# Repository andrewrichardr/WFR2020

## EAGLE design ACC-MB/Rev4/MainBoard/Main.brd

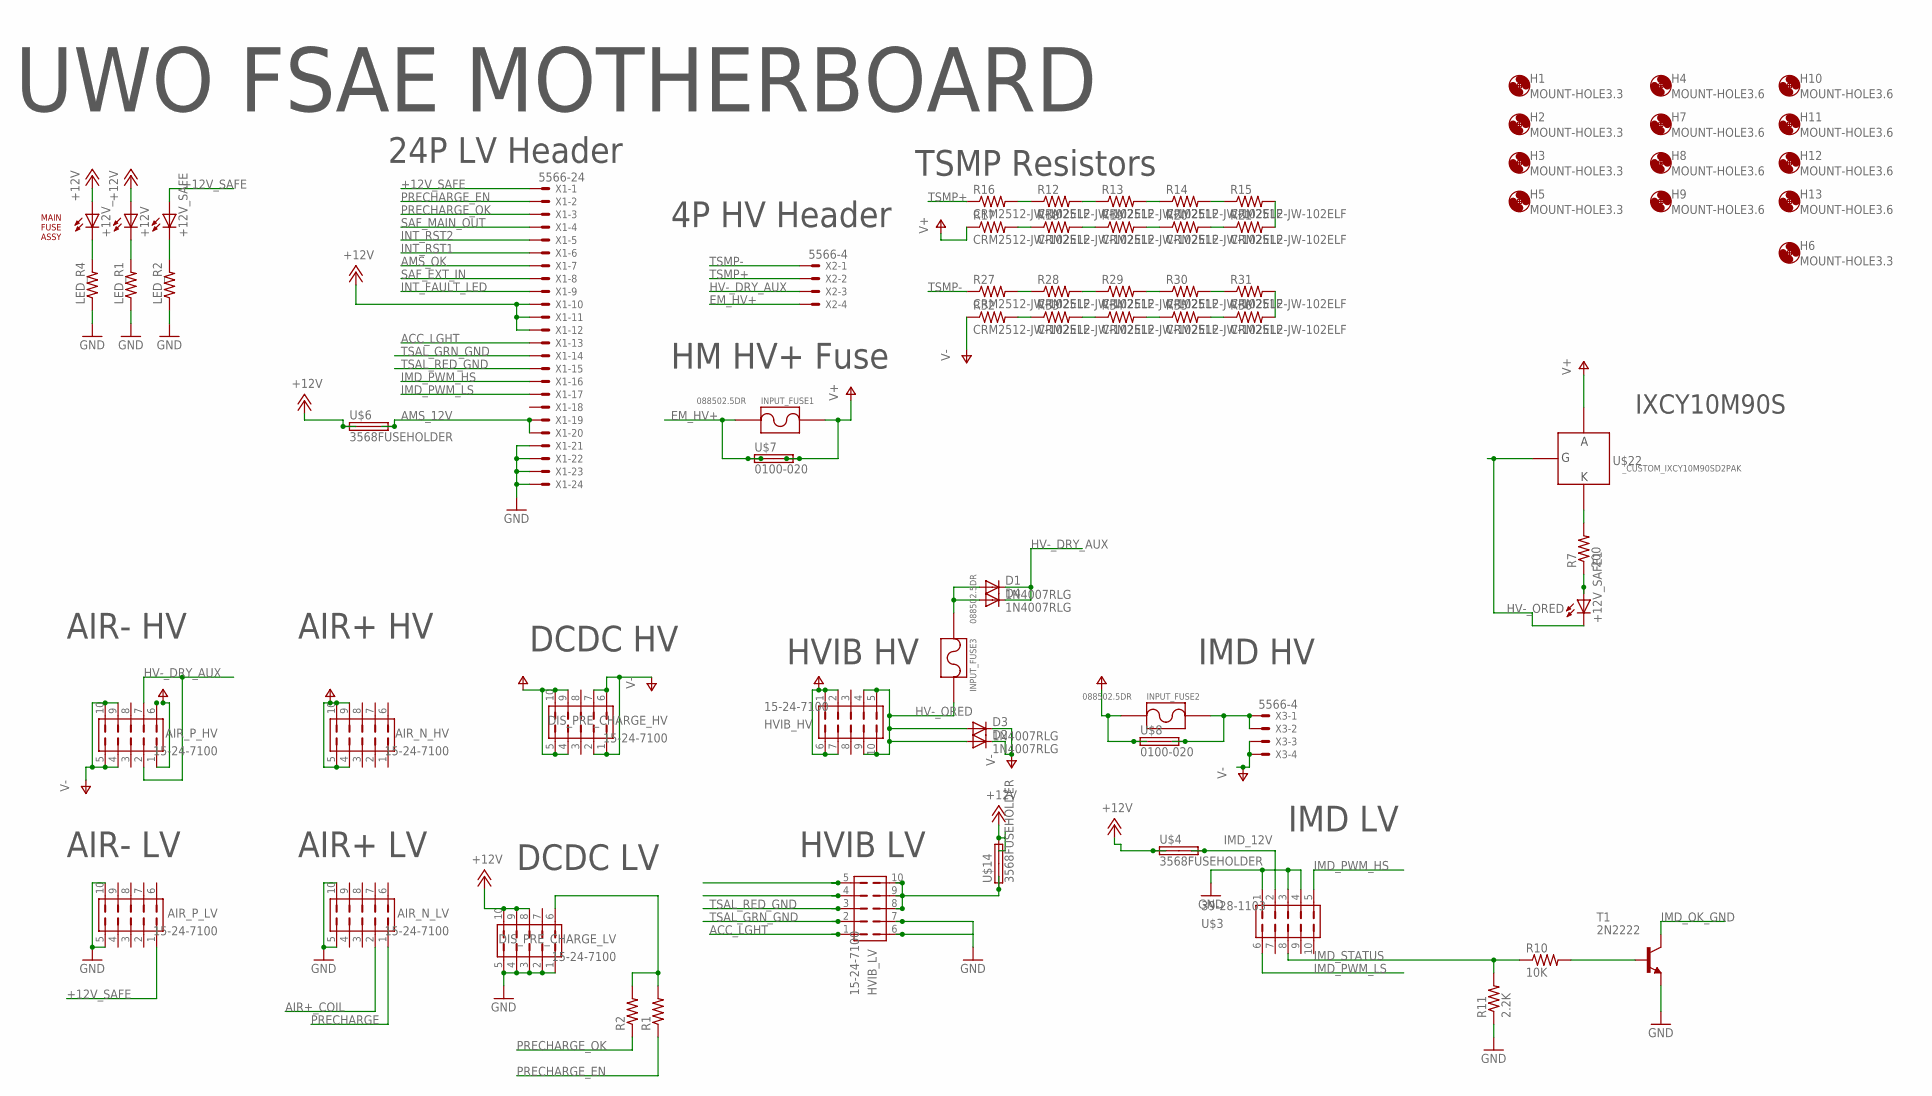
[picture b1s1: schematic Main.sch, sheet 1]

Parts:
+12V, +12V_, +12V_SAFE: LEDCHIP-LED0805; CHIP-LED0805
+12V_SAFE1: LED5MM
AIR_N_HV: 15-24-7100; 5566-10-BMI
AIR_N_LV: 15-24-7100; 5566-10-BMI
AIR_P_HV: 15-24-7100; 5566-10-BMI
AIR_P_LV: 15-24-7100; 5566-10-BMI
D1, D2, D3, D4: 1N4007RLG; DO41-10
DIS_PRE_CHARGE_HV: 15-24-7100; 5566-10-BMI
DIS_PRE_CHARGE_LV: 15-24-7100; 5566-10-BMI
H1, H2, H3, H5, H6: MOUNT-HOLE3.3; 3,3
H4, H7, H8, H9, H10, H11, H12, H13: MOUNT-HOLE3.6; 3,6
HVIB_HV: 15-24-7100; 5566-10-BMI
HVIB_LV: 15-24-7100; 5566-10-BMI
INPUT_FUSE1, INPUT_FUSE2, INPUT_FUSE3: 088502.5DR; _CUSTOM_PARTS_LF_885
LED_R1, LED_R2, LED_R4: R-US_R0805; R0805
R1, R2: R-US_R0805; R0805
R7: 200; R2010
R10: 10K; M0805
R11: 2.2K; M0805
R12, R13, R14, R15, R16, R17, R18, R19, R20, R21, R27, R28, R29, R30, R31, R32, R33, R34, R35, R36: CRM2512-JW-102ELF; R2512
T1: 2N2222; TO92-EBC-OVAL
U$1: MAINFUSEASSY
U$3: 39-28-1103
U$4, U$6, U$14: 3568FUSEHOLDER; 3568
U$7, U$8: 0100-020
U$22: _CUSTOM_IXCY10M90SD2PAK; TO228P991X238-3
X1: 5566-24
X2, X3: 5566-4

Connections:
+12V: +12V.A, +12V_.A, DIS_PRE_CHARGE_LV.8, DIS_PRE_CHARGE_LV.9, DIS_PRE_CHARGE_LV.10, U$4.L1 (1A), U$4.L2 (1B), U$6.L1 (1A), U$6.L2 (1B), U$14.R1 (2A), U$14.R2 (2B), X1.10, X1.11, X1.12; also elsewhere on the board
+12V_SAFE: +12V_SAFE.A, AIR_P_LV.1, X1.1; also elsewhere on the board
ACC_LGHT: HVIB_LV.1, X1.13
AIR+_COIL: AIR_N_LV.2; also elsewhere on the board
AMS_12V: U$6.R1 (2A), U$6.R2 (2B), X1.19, X1.20
AMS_OK: X1.7; also elsewhere on the board
EM_HV+: INPUT_FUSE1.P$1, U$7.P$1 (1A), U$7.P$3 (1B), X2.4
GND: AIR_N_LV.5, AIR_N_LV.10, AIR_P_LV.5, AIR_P_LV.10, DIS_PRE_CHARGE_LV.1, DIS_PRE_CHARGE_LV.2, DIS_PRE_CHARGE_LV.3, DIS_PRE_CHARGE_LV.4, DIS_PRE_CHARGE_LV.5, HVIB_LV.7, LED_R1.1, LED_R2.1, LED_R4.1, R11.1, T1.E, U$3.1, U$3.3, U$3.4, X1.21, X1.22, X1.23, X1.24; also elsewhere on the board
HV-_DRY_AUX: AIR_P_HV.2, AIR_P_HV.7, D1.C, D4.C, X2.3
HV-_ORED: +12V_SAFE1.K (C), D2.A, D3.A, HVIB_HV.4, HVIB_HV.5, HVIB_HV.9, HVIB_HV.10, INPUT_FUSE3.P$2, U$22.1 (G)
IMD_12V: U$3.2, U$4.R1 (2A), U$4.R2 (2B)
IMD_OK_GND: T1.C; also elsewhere on the board
IMD_PWM_HS: U$3.5, X1.16
IMD_PWM_LS: U$3.6, X1.17
IMD_STATUS: R10.1, R11.2, U$3.8
INT_FAULT_LED: X1.9; also elsewhere on the board
INT_RST1: X1.6; also elsewhere on the board
INT_RST2: X1.5; also elsewhere on the board
unnamed: +12V.C, LED_R1.2
unnamed: R10.2, T1.B
unnamed: +12V_.C, LED_R4.2
unnamed: +12V_SAFE.C, LED_R2.2
unnamed: R12.1, R16.2
unnamed: R12.2, R13.1
unnamed: R13.2, R14.1
unnamed: R14.2, R15.1
unnamed: R15.2, R21.2
unnamed: R20.2, R21.1
unnamed: R19.2, R20.1
unnamed: R18.2, R19.1
unnamed: R17.2, R18.1
unnamed: DIS_PRE_CHARGE_LV.6, R1.2, R2.2
unnamed: INPUT_FUSE2.P$2, U$8.P$2 (2A), U$8.P$4 (2B), X3.1, X3.2
unnamed: R7.2, U$22.2 (K)
unnamed: R27.2, R28.1
unnamed: R28.2, R29.1
unnamed: R29.2, R30.1
unnamed: R30.2, R31.1
unnamed: R31.2, R36.2
unnamed: R35.2, R36.1
unnamed: R34.2, R35.1
unnamed: R33.2, R34.1
unnamed: R32.2, R33.1
unnamed: +12V_SAFE1.A, R7.1
unnamed: HVIB_LV.8, HVIB_LV.9, HVIB_LV.10, U$14.L1 (1A), U$14.L2 (1B)
unnamed: D1.A, D4.A, INPUT_FUSE3.P$1
PRECHARGE: AIR_N_LV.1; also elsewhere on the board
PRECHARGE_EN: R1.1, X1.2; also elsewhere on the board
PRECHARGE_OK: R2.1, X1.3; also elsewhere on the board
SAF_EXT_IN: X1.8; also elsewhere on the board
SAF_MAIN_OUT: X1.4; also elsewhere on the board
TSAL_GRN_GND: HVIB_LV.2, X1.14
TSAL_RED_GND: HVIB_LV.3, X1.15
TSMP+: R16.1, X2.2
TSMP-: R27.1, X2.1
V+: AIR_N_HV.4, AIR_N_HV.5, AIR_N_HV.9, AIR_N_HV.10, AIR_P_HV.1, AIR_P_HV.6, DIS_PRE_CHARGE_HV.4, DIS_PRE_CHARGE_HV.5, DIS_PRE_CHARGE_HV.9, DIS_PRE_CHARGE_HV.10, HVIB_HV.1, HVIB_HV.2, HVIB_HV.6, HVIB_HV.7, INPUT_FUSE1.P$2, INPUT_FUSE2.P$1, R17.1, U$7.P$2 (2A), U$7.P$4 (2B), U$8.P$1 (1A), U$8.P$3 (1B), U$22.3 (A)
V-: AIR_P_HV.4, AIR_P_HV.5, AIR_P_HV.9, AIR_P_HV.10, D2.C, D3.C, DIS_PRE_CHARGE_HV.1, DIS_PRE_CHARGE_HV.2, DIS_PRE_CHARGE_HV.6, DIS_PRE_CHARGE_HV.7, R32.1, X3.3, X3.4

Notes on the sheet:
UWO FSAE MOTHERBOARD
TSMP Resistors
24P LV Header
4P HV Header
HM HV+ Fuse
AIR- HV
AIR- LV
AIR+ LV
AIR+ HV
DCDC HV
DCDC LV
HVIB HV
HVIB LV
IMD HV
IMD LV
IXCY10M90S

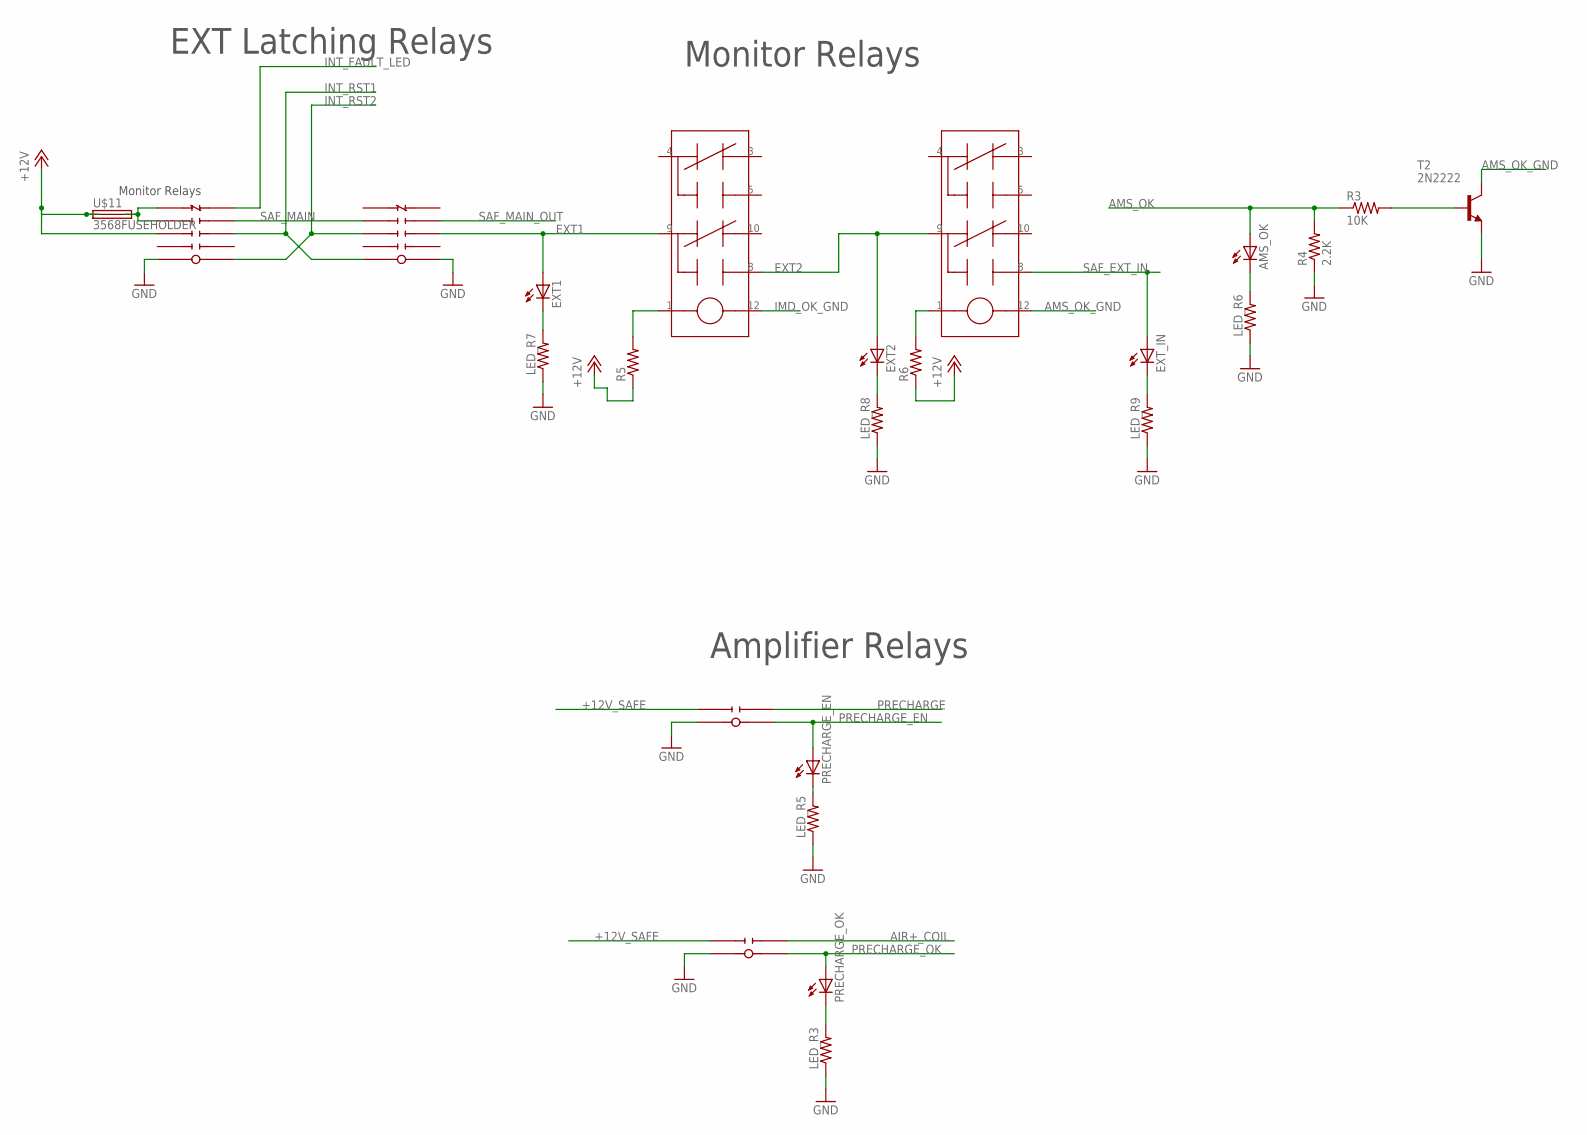
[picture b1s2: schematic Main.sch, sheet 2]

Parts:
AMS_OK: LEDCHIP-LED0805; CHIP-LED0805
EXT1, EXT2: LEDCHIP-LED0805; CHIP-LED0805
EXT_IN: LEDCHIP-LED0805; CHIP-LED0805
LED_R3, LED_R5, LED_R6, LED_R7, LED_R8, LED_R9: R-US_R0805; R0805
PRECHARGE_EN: LEDCHIP-LED0805; CHIP-LED0805
PRECHARGE_OK: LEDCHIP-LED0805; CHIP-LED0805
R3: 10K; M0805
R4: 2.2K; M0805
R5, R6: R-US_R0805; R0805
T2: 2N2222; TO92-EBC-OVAL
U$2, U$5: SR4M4012_TE; SR4M4012_FOOT
U$9, U$10: G5NB-1A-E
U$11: 3568FUSEHOLDER; 3568
U$12, U$13: V23079B1203B301

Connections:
+12V: R5.1, R6.1, U$2.NOA2, U$11.L1 (1A), U$11.L2 (1B); also elsewhere on the board
+12V_SAFE: U$9.2 (NOA1), U$10.2 (NOA1); also elsewhere on the board
AIR+_COIL: U$9.3 (NOB1); also elsewhere on the board
AMS_OK: AMS_OK.A, R3.1, R4.2; also elsewhere on the board
AMS_OK_GND: T2.C, U$13.12
EXT1: EXT1.A, U$5.NOB2, U$12.9
EXT2: EXT2.A, U$12.8, U$13.9
GND: LED_R3.1, LED_R5.1, LED_R6.1, LED_R7.1, LED_R8.1, LED_R9.1, R4.1, T2.E, U$2.COIL+, U$5.COIL-, U$9.1 (COIL+), U$10.1 (COIL+); also elsewhere on the board
IMD_OK_GND: U$12.12; also elsewhere on the board
INT_FAULT_LED: U$2.NCB4; also elsewhere on the board
INT_RST1: U$2.NOB2, U$5.COIL+; also elsewhere on the board
INT_RST2: U$2.COIL-, U$5.NOA2; also elsewhere on the board
unnamed: U$2.NCA4, U$2.NOA3, U$11.R1 (2A), U$11.R2 (2B)
unnamed: LED_R5.2, PRECHARGE_EN.C
unnamed: LED_R3.2, PRECHARGE_OK.C
unnamed: AMS_OK.C, LED_R6.2
unnamed: EXT1.C, LED_R7.2
unnamed: EXT2.C, LED_R8.2
unnamed: EXT_IN.C, LED_R9.2
unnamed: R3.2, T2.B
unnamed: R5.2, U$12.1
unnamed: R6.2, U$13.1
PRECHARGE: U$10.3 (NOB1); also elsewhere on the board
PRECHARGE_EN: PRECHARGE_EN.A, U$10.4 (COIL-); also elsewhere on the board
PRECHARGE_OK: PRECHARGE_OK.A, U$9.4 (COIL-); also elsewhere on the board
SAF_EXT_IN: EXT_IN.A, U$13.8; also elsewhere on the board
SAF_MAIN: U$2.NOB3, U$5.NOA3
SAF_MAIN_OUT: U$5.NOB3; also elsewhere on the board

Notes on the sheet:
Monitor Relays
EXT Latching Relays
Amplifier Relays

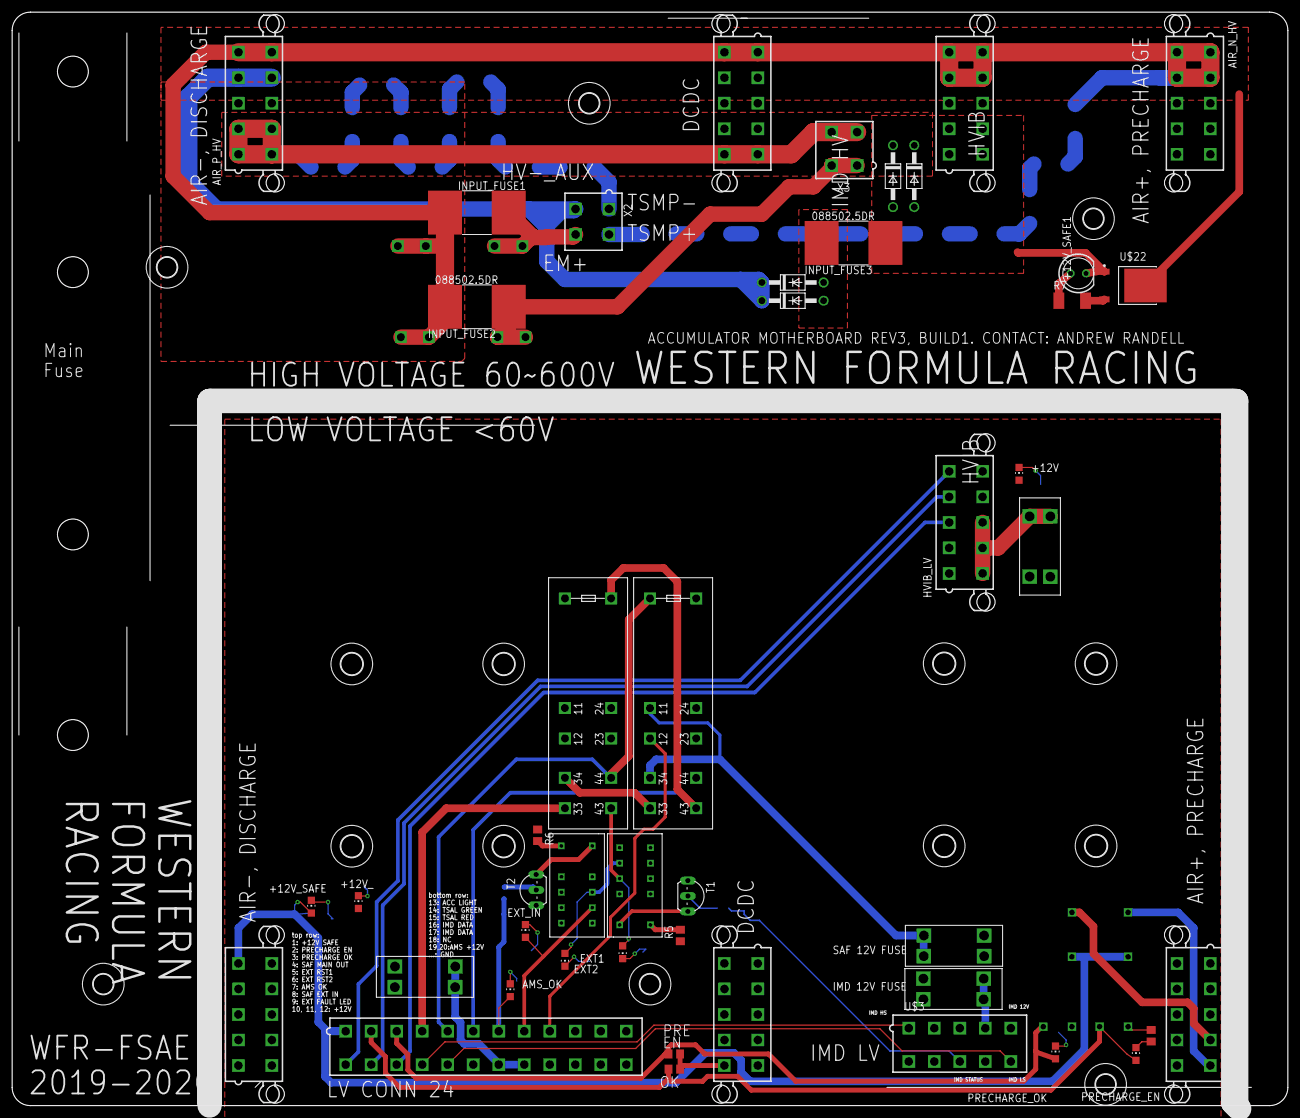
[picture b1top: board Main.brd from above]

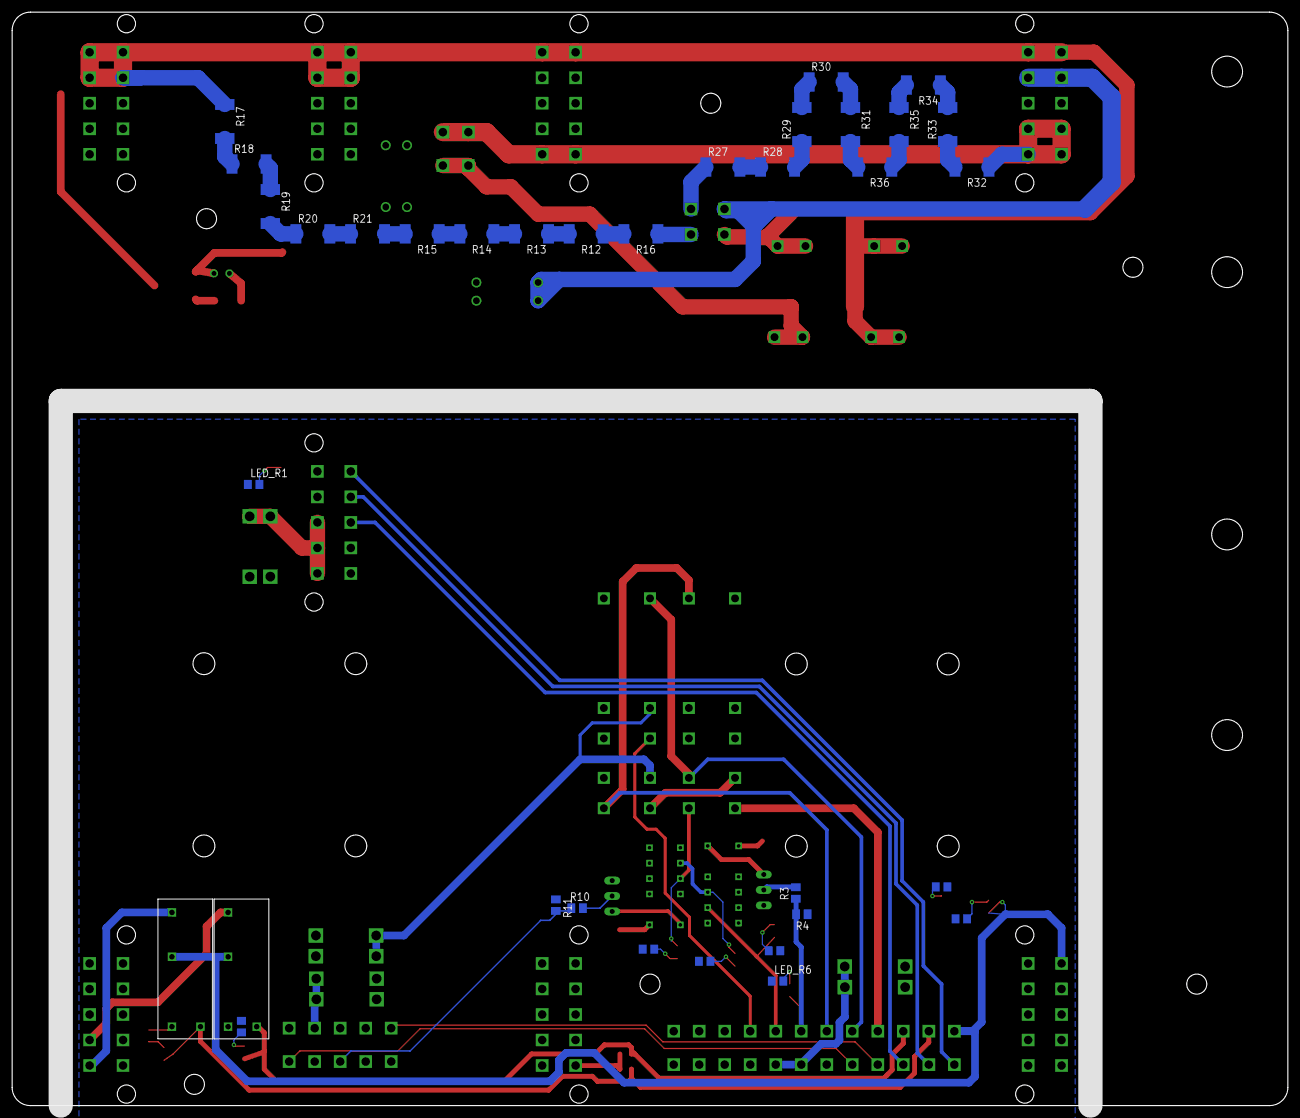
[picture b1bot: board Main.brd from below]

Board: 2 copper layers, 210.0 x 180.0 mm, 97 parts (34 on the bottom side), 71 nets.

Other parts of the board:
H14: MOUNT-HOLE3.3; 3,3

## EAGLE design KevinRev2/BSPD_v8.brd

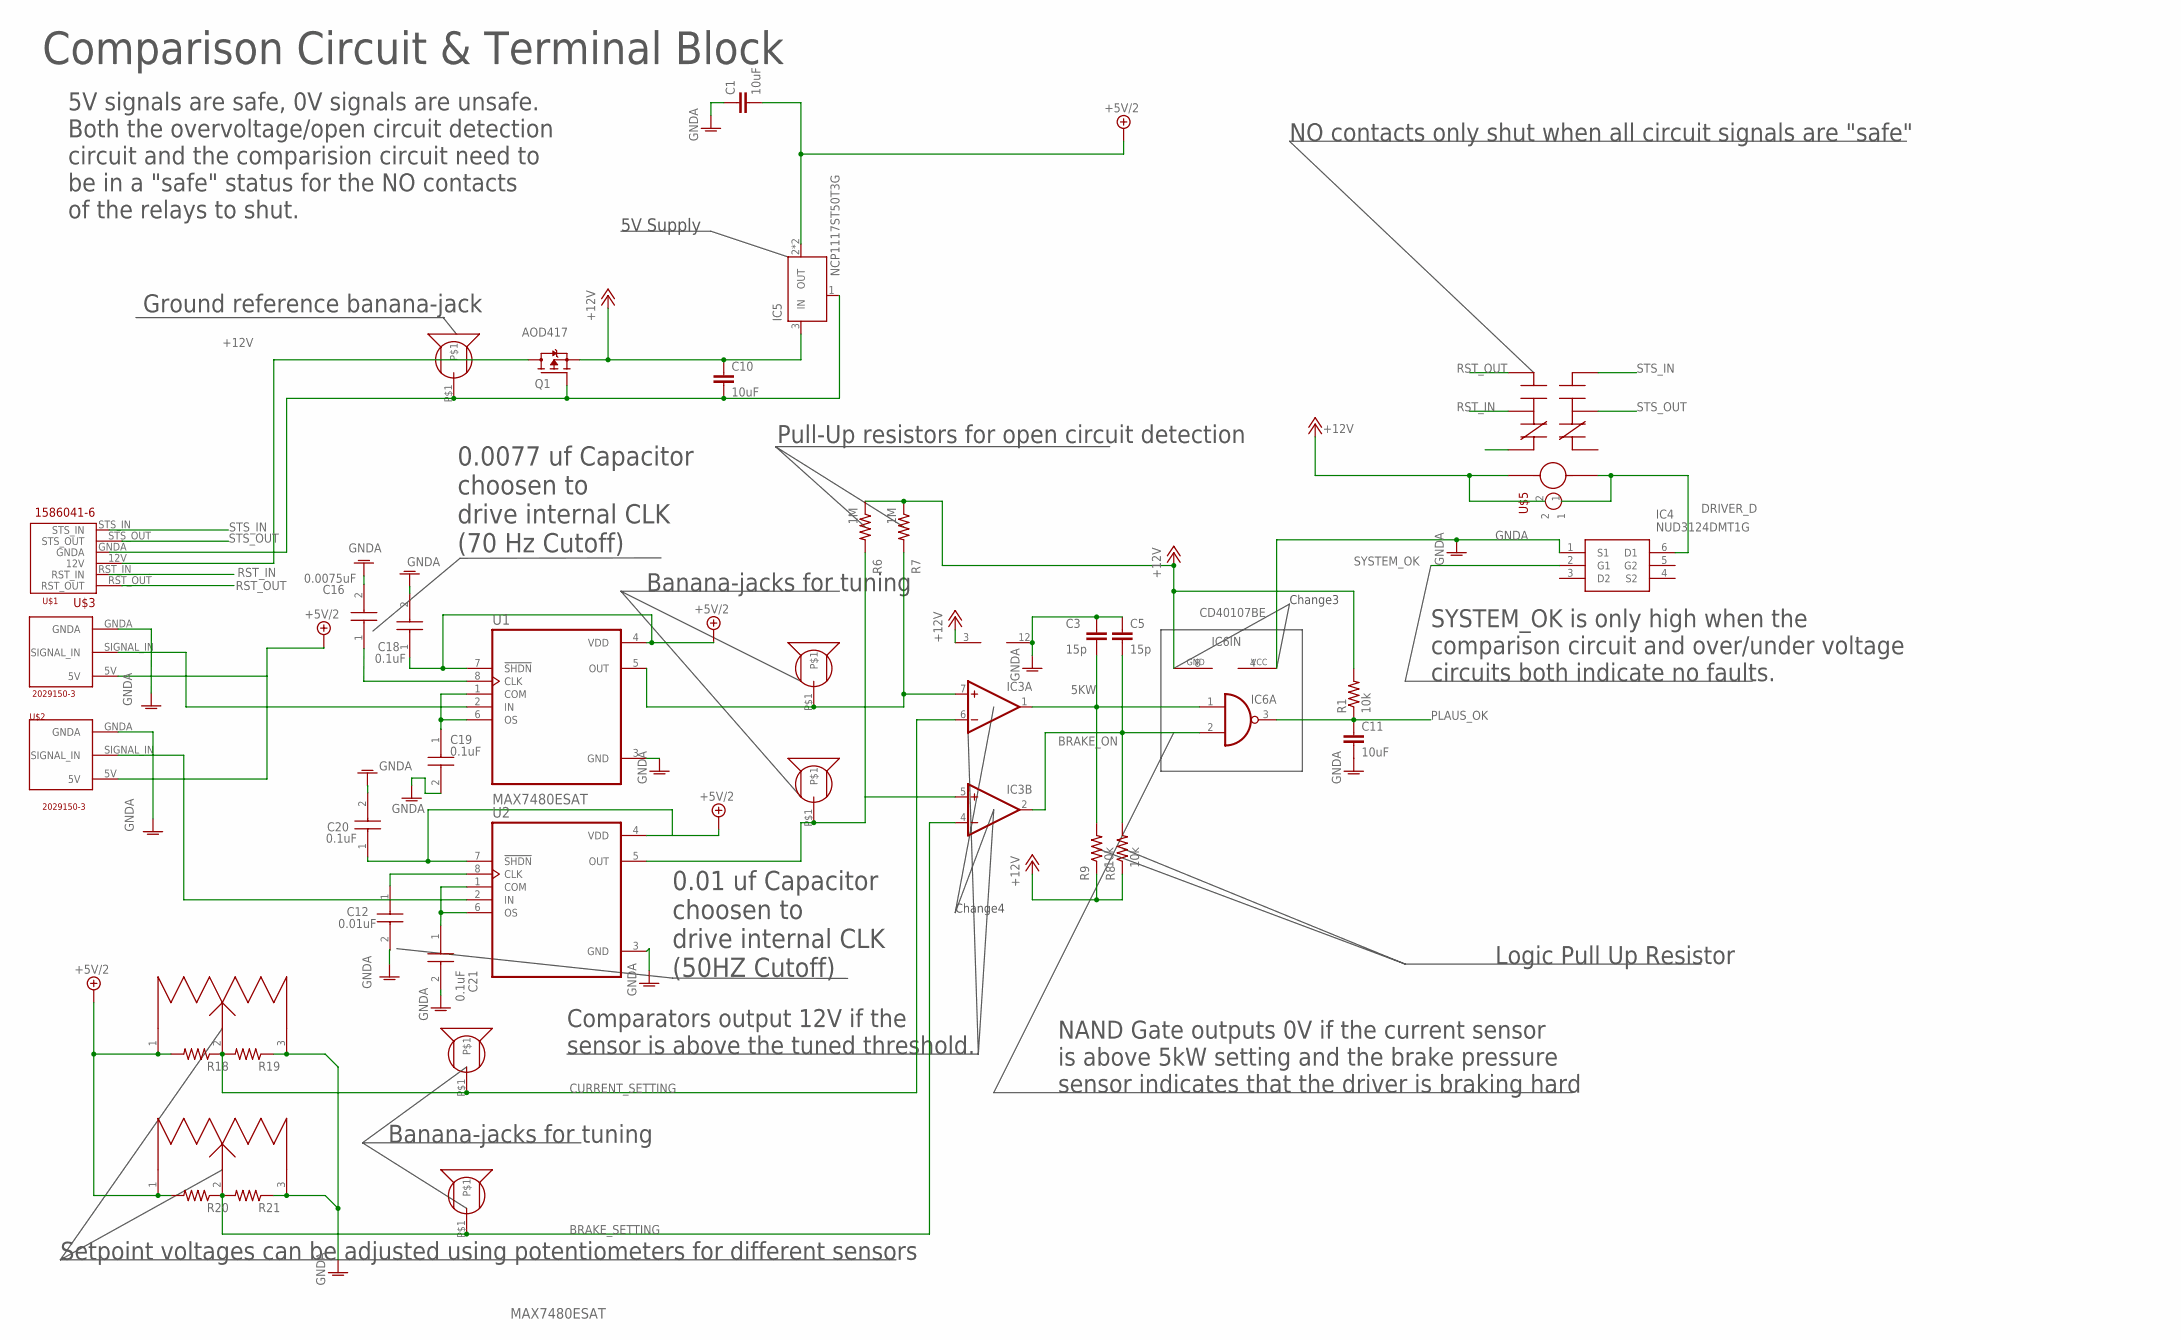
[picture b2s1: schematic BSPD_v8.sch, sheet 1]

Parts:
C1, C10, C11: 10uF; C0805
C3, C5: 15p; C0805
C12: 0.01uF; CAPC2012X95N
C16: 0.0075uF; CAPC2012X95N
C18, C19, C20, C21: 0.1uF; CAPC2012X140N
IC3: 4AMP_P11+7N; DIL14
IC4: NUD3124DMT1G; SOT95P275X110-6N
IC5: NCP1117ST50T3G; SOT223
IC6: CD40107BE; DIL08
Q1: AOD417; TO252
R1, R8, R9: 10k; M0805
R6, R7: 1M; M0805
R18, R19, R20, R21: R-US_M0805; M0805
U1, U2: MAX7480ESAT; SOIC127P600X175-8N
U$1, U$2: 2029150-3
U$3: 1586041-6
U$4, U$13, U$14, U$18, U$19: BSPD_PARTS_MP_BANANA_PLUG; BSPD_PARTS_BANANA_PLUG
U$5: SSL-LX3044ID-12V
U$10, U$11: PTC10LV10-103A1010
U$12: BSPD_PARTS_RLY_V23079A1001B301; BSPD_PARTS_V23079F1101B301

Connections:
5KW: C3.2, IC3.1 (OUT), IC6.1 (I0), R9.2
12V: Q1.3 (D), U$3.12V
+5V/2: C1.2, C18.1, C20.1, IC5.2 (OUT), IC5.4 (OUT), R18.2, R20.2, U1.4 (VDD), U1.7 (!SHDN), U2.4 (VDD), U2.7 (!SHDN), U$1.5V, U$2.5V, U$10.1 (CW), U$11.1 (CW); also elsewhere on the board
+12V: C10.1, IC3.3 (V+), IC5.3 (IN), IC6.8 (GND), Q1.2 (S), R1.2, R6.1, R7.1, R8.1, R9.1, U$5.2, U$12.1; also elsewhere on the board
BRAKE_ON: C5.2, IC3.2 (OUT), IC6.2 (I1), R8.2
BRAKE_PRES_IN: IC3.5 (+IN), R6.2, U2.5 (OUT), U$14.P$1; also elsewhere on the board
BRAKE_SETTING: IC3.4 (-IN), R20.1, R21.2, U$10.2 (VO), U$19.P$1
CURRENT_IN: IC3.7 (+IN), R7.2, U1.5 (OUT), U$13.P$1; also elsewhere on the board
CURRENT_SETTING: IC3.6 (-IN), R18.1, R19.2, U$11.2 (VO), U$18.P$1
DRIVER_D: IC4.6 (D1), U$5.1, U$12.12
GNDA: C1.1, C3.1, C5.1, C10.2, C11.2, C12.2, C16.2, C18.2, C19.2, C20.2, C21.2, IC3.12 (V-), IC4.1 (S1), IC5.1 (GND), IC6.4 (VCC), Q1.1 (G), R19.1, R21.1, U1.3 (GND), U2.3 (GND), U$1.GNDA, U$2.GNDA, U$3.GNDA, U$4.P$1, U$10.3 (CCW), U$11.3 (CCW); also elsewhere on the board
unnamed: U2.2 (IN), U$2.SIGNAL_IN
unnamed: U1.2 (IN), U$1.SIGNAL_IN
unnamed: C19.1, U1.1 (COM), U1.6 (OS)
unnamed: C21.1, U2.1 (COM), U2.6 (OS)
unnamed: C12.1, U2.8 (CLK)
unnamed: C16.1, U1.8 (CLK)
PLAUS_OK: C11.1, IC6.3 (O), R1.1; also elsewhere on the board
RST_IN: U$3.RST_IN, U$12.4
RST_OUT: U$3.RST_OUT, U$12.5
STS_IN: U$3.STS_IN, U$12.8
STS_OUT: U$3.STS_OUT, U$12.9
SYSTEM_OK: IC4.2 (G1); also elsewhere on the board

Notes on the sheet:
Comparison Circuit & Terminal Block
Logic Pull Up Resistor
Pull-Up resistors for open circuit detection
Banana-jacks for tuning
Setpoint voltages can be adjusted using potentiometers for different sensors
Ground reference banana-jack
5V Supply
NO contacts only shut when all circuit signals are "safe"
5V signals are safe, 0V signals are unsafe. Both the overvoltage/open circuit detection circuit and the comparision circuit need to be in a "safe" status for the NO contacts of the relays to shut.
NAND Gate outputs 0V if the current sensor is above 5kW setting and the brake pressure sensor indicates that the driver is braking hard
Comparators output 12V if the sensor is above the tuned threshold.
SYSTEM_OK is only high when the comparison circuit and over/under voltage circuits both indicate no faults.
Change3
Change4
0.0077 uf Capacitor choosen to drive internal CLK (70 Hz Cutoff)
0.01 uf Capacitor choosen to drive internal CLK (50HZ Cutoff)

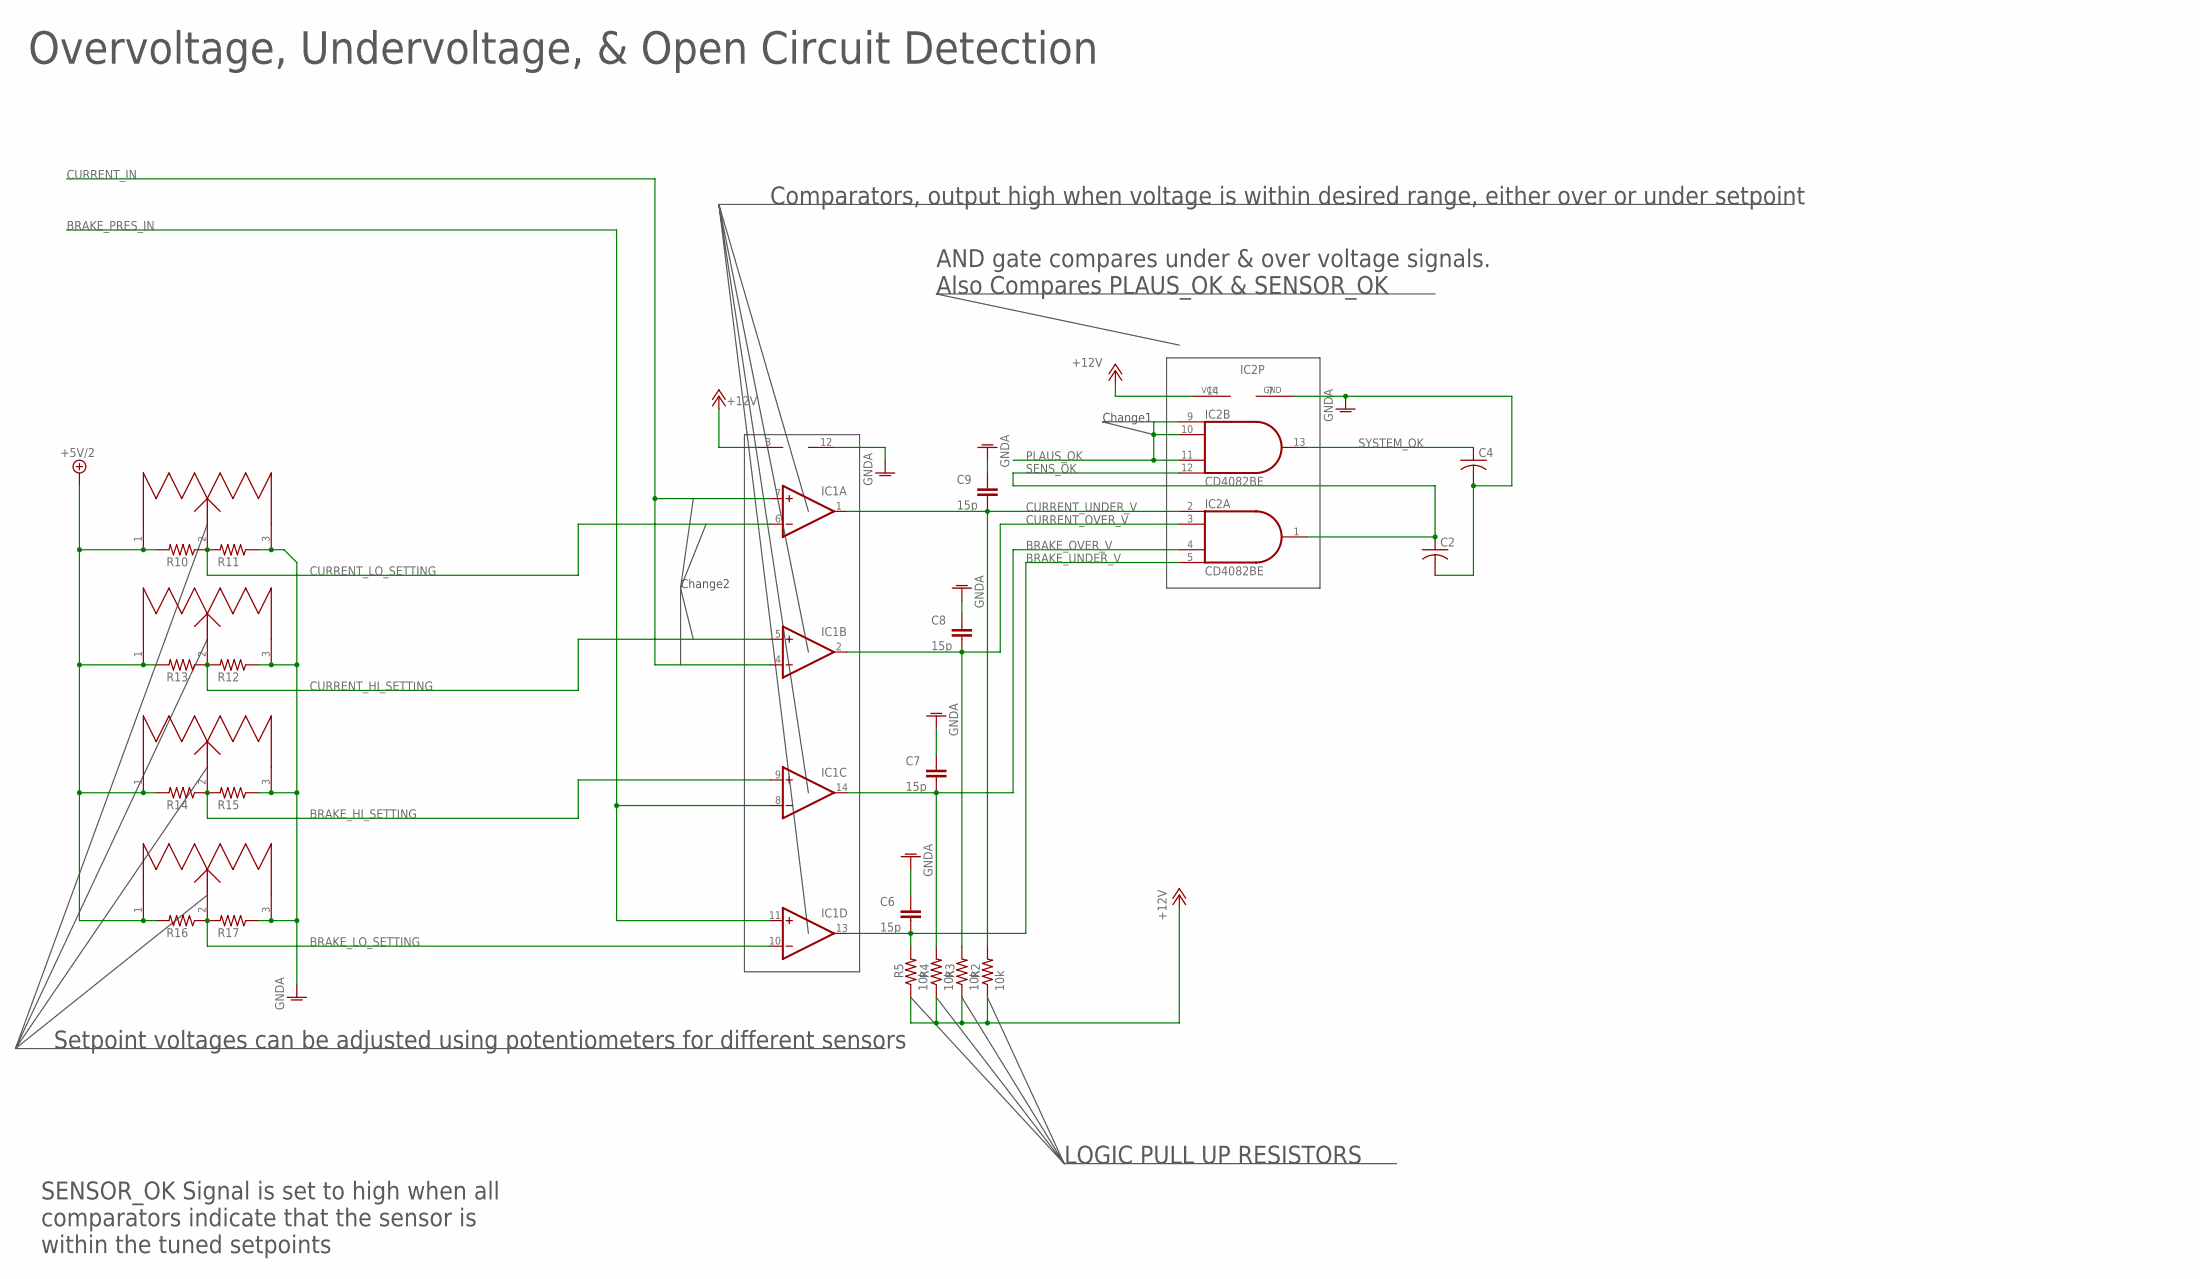
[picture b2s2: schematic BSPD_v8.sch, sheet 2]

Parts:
C2, C4: C-USC0805; C0805
C6, C7, C8, C9: 15p; C0805
IC1: 4AMP_P11+7N; DIL14
IC2: CD4082BE; DIL14
R2, R3, R4, R5: 10k; M0805
R10, R11, R12, R13, R14, R15, R16, R17: R-US_M0805; M0805
U$6, U$7, U$8, U$9: PTC10LV10-103A1010

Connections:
+5V/2: R10.2, R13.2, R14.2, R16.2, U$6.1 (CW), U$7.1 (CW), U$8.1 (CW), U$9.1 (CW); also elsewhere on the board
+12V: IC1.3 (V+), IC2.14 (VCC), R2.1, R3.1, R4.1, R5.1; also elsewhere on the board
BRAKE_HI_SETTING: IC1.9 (+IN), R14.1, R15.2, U$8.2 (VO)
BRAKE_LO_SETTING: IC1.10 (-IN), R16.1, R17.2, U$9.2 (VO)
BRAKE_OVER_V: C7.2, IC1.14 (OUT), IC2.4 (I2), R4.2
BRAKE_PRES_IN: IC1.8 (-IN), IC1.11 (+IN); also elsewhere on the board
BRAKE_UNDER_V: C6.2, IC1.13 (OUT), IC2.5 (I3), R5.2
CURRENT_HI_SETTING: IC1.5 (+IN), R12.2, R13.1, U$7.2 (VO)
CURRENT_IN: IC1.4 (-IN), IC1.7 (+IN); also elsewhere on the board
CURRENT_LO_SETTING: IC1.6 (-IN), R10.1, R11.2, U$6.2 (VO)
CURRENT_OVER_V: C8.2, IC1.2 (OUT), IC2.3 (I1), R3.2
CURRENT_UNDER_V: C9.2, IC1.1 (OUT), IC2.2 (I0), R2.2
GNDA: C2.2, C4.2, C6.1, C7.1, C8.1, C9.1, IC1.12 (V-), IC2.7 (GND), R11.1, R12.1, R15.1, R17.1, U$6.3 (CCW), U$7.3 (CCW), U$8.3 (CCW), U$9.3 (CCW); also elsewhere on the board
PLAUS_OK: IC2.9 (I0), IC2.10 (I1), IC2.11 (I2); also elsewhere on the board
SENS_OK: C2.1, IC2.1 (O), IC2.12 (I3)
SYSTEM_OK: C4.1, IC2.13 (O); also elsewhere on the board

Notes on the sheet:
Overvoltage, Undervoltage, & Open Circuit Detection
Setpoint voltages can be adjusted using potentiometers for different sensors
AND gate compares under & over voltage signals. Also Compares PLAUS_OK & SENSOR_OK
Comparators, output high when voltage is within desired range, either over or under setpoint
SENSOR_OK Signal is set to high when all comparators indicate that the sensor is within the tuned setpoints
LOGIC PULL UP RESISTORS
Change1
Change2

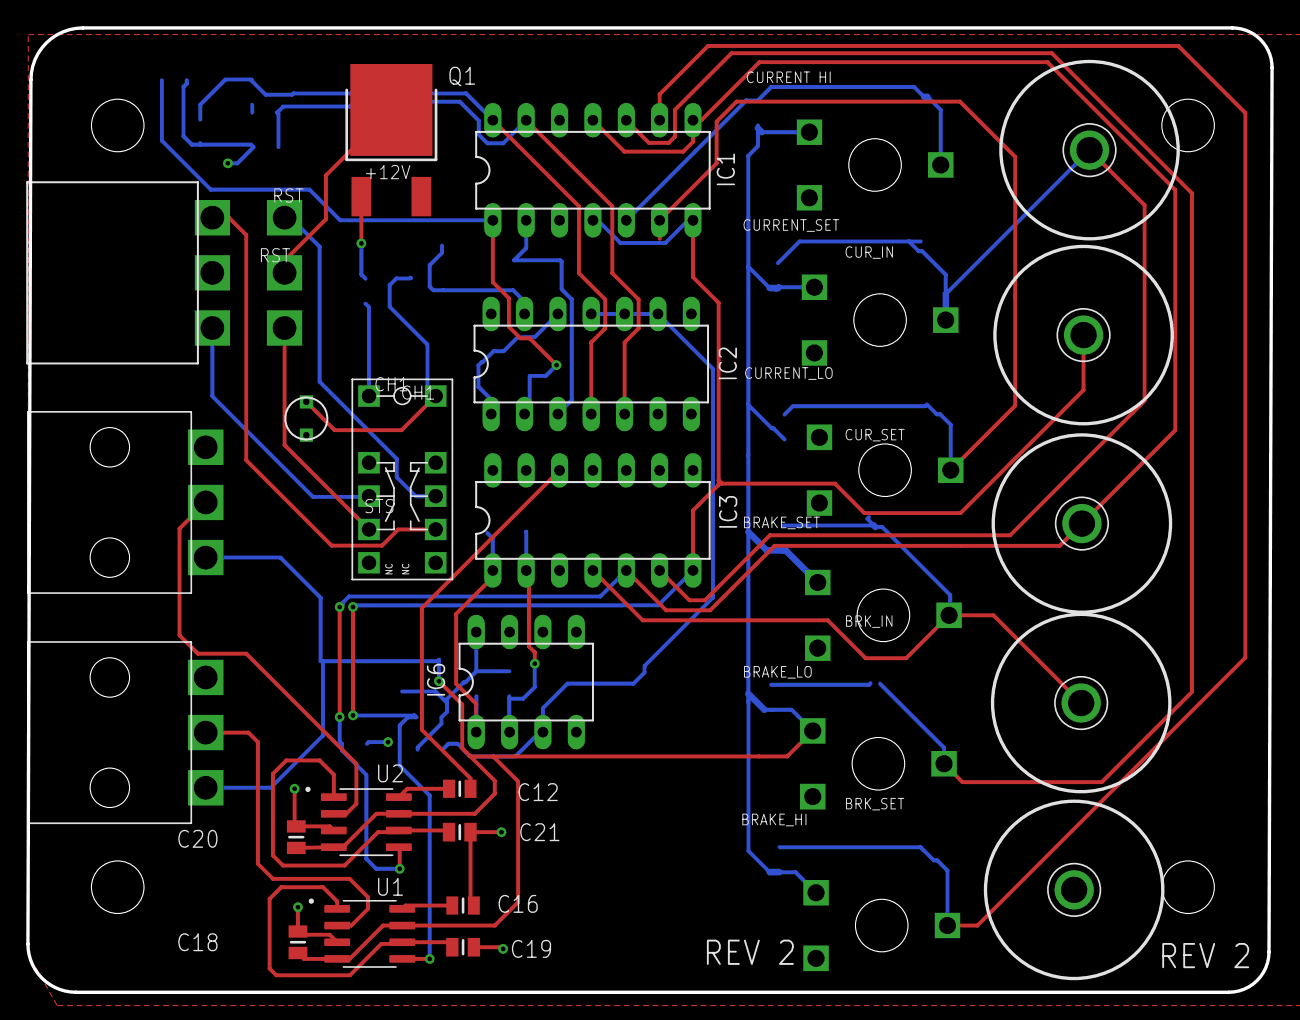
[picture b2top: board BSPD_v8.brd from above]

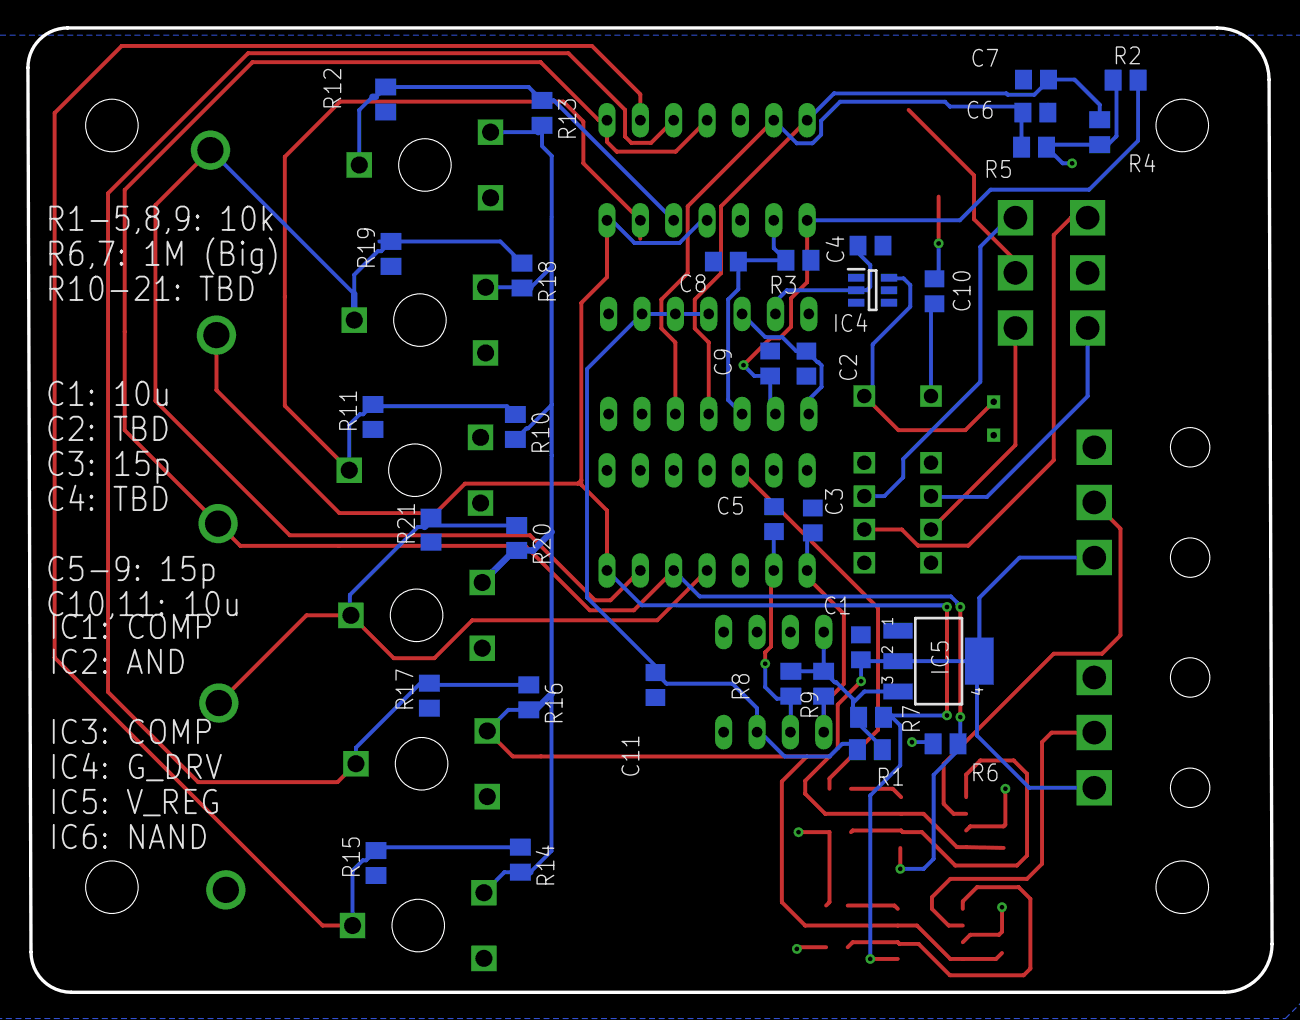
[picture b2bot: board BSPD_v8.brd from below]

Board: 2 copper layers, 94.7 x 73.4 mm, 63 parts (34 on the bottom side), 32 nets.

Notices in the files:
parts and their libraries:
SparkFun-IC-Special-Function: Licensing: Creative Commons ShareAlike 4.0 International - https://creativecommons.org/licenses/by-sa/4.0
COPYRIGHT: Copyright (C) 2018 Accelerated Designs. All rights reserved
COPYRIGHT: Copyright (C) 2016 Accelerated Designs. All rights reserved
